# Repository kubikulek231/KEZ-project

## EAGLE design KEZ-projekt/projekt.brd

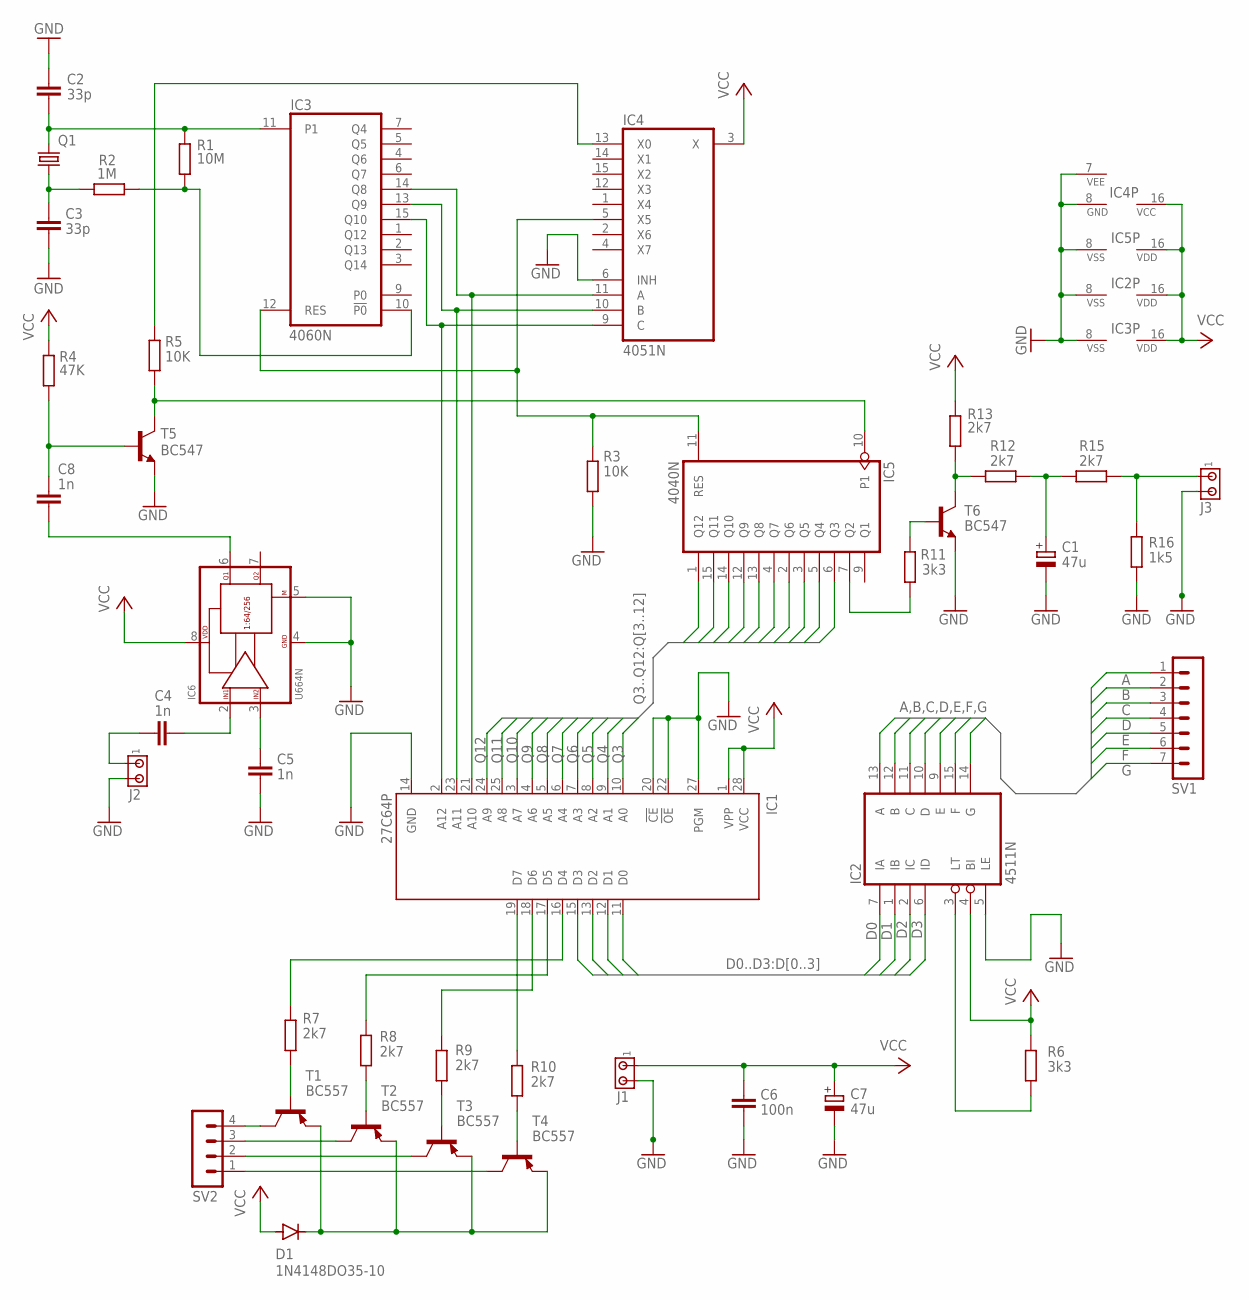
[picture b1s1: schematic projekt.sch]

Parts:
C1, C7: 47u; E2,5-6
C2, C3: 33p; C025-025X050
C4, C5, C8: 1n; C025-025X050
C6: 100n; C025-025X050
D1: 1N4148DO35-10; DO35-10
IC1: 27C64P; DIL28-6
IC2: 4511N; DIL16
IC3: 4060N; DIL16
IC4: 4051N; DIL16
IC5: 4040N; DIL16
IC6: U664N; DIL08
J1, J2, J3: MTA02-100; 10X02MTA
Q1: CRYSTALHC49S; HC49/S
R1: 10M; 0207/10
R2: 1M; 0207/10
R3, R5: 10K; 0207/10
R4: 47K; 0207/10
R6, R11: 3k3; 0207/10
R7, R8, R9, R10, R12, R13, R15: 2k7; 0207/10
R16: 1k5; 0207/10
SV1: MA07-1
SV2: MA04-1
T1, T2, T3, T4: BC557; TO92
T5, T6: BC547; TO92

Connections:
A: IC2.13 (A), SV1.1
B: IC2.12 (B), SV1.2
C: IC2.11 (C), SV1.3
D: IC2.10 (D), SV1.4
D0: IC1.11 (D0), IC2.7 (IA)
D1: IC1.12 (D1), IC2.1 (IB)
D2: IC1.13 (D2), IC2.2 (IC)
D3: IC1.15 (D3), IC2.6 (ID)
E: IC2.9 (E), SV1.5
F: IC2.15 (F), SV1.6
G: IC2.14 (G), SV1.7
GND: C1.-, C2.1, C3.2, C5.2, C6.2, C7.-, IC1.14 (GND), IC1.20 (!CE), IC1.22 (!OE), IC1.27 (PGM), IC2.5 (LE), IC2.8 (VSS), IC3.8 (VSS), IC4.6 (INH), IC4.7 (VEE), IC4.8 (GND), IC5.8 (VSS), IC6.4 (GND), IC6.5 (FAKT), J1.2, J2.2, J3.2, R3.1, R16.1, T5.1 (E), T6.1 (E)
unnamed: C2.2, IC3.11 (P1), Q1.2, R1.2
unnamed: C3.1, Q1.1, R2.2
unnamed: IC3.10 (!P0), R1.1, R2.1
unnamed: IC1.21 (A10), IC3.14 (Q8), IC4.11 (A)
unnamed: IC1.23 (A11), IC3.13 (Q9), IC4.10 (B)
unnamed: IC1.2 (A12), IC3.15 (Q10), IC4.9 (C)
unnamed: IC3.12 (RES), IC4.5 (X5), IC5.11 (RES), R3.2
unnamed: C8.1, R4.1, T5.2 (B)
unnamed: C8.2, IC6.6 (O1)
unnamed: C5.1, IC6.3 (I2)
unnamed: C4.2, IC6.2 (I1)
unnamed: IC5.10 (P1), R5.1, T5.3 (C)
unnamed: C4.1, J2.1
unnamed: R12.1, R13.2, T6.3 (C)
unnamed: IC2.3 (LT), R6.2
unnamed: IC1.17 (D5), R8.2
unnamed: IC1.16 (D4), R7.2
unnamed: IC1.18 (D6), R9.2
unnamed: IC1.19 (D7), R10.2
unnamed: D1.C, T1.1 (E), T2.1 (E), T3.1 (E), T4.1 (E)
unnamed: R9.1, T3.2 (B)
unnamed: R8.1, T2.2 (B)
unnamed: R7.1, T1.2 (B)
unnamed: SV2.4, T1.3 (C)
unnamed: SV2.3, T2.3 (C)
unnamed: SV2.2, T3.3 (C)
unnamed: SV2.1, T4.3 (C)
unnamed: R10.1, T4.2 (B)
unnamed: IC5.7 (Q2), R11.1
unnamed: R11.2, T6.2 (B)
unnamed: C1.+, R12.2, R15.1
unnamed: J3.1, R15.2, R16.2
unnamed: IC4.13 (X0), R5.2
Q3: IC1.10 (A0), IC5.6 (Q3)
Q4: IC1.9 (A1), IC5.5 (Q4)
Q5: IC1.8 (A2), IC5.3 (Q5)
Q6: IC1.7 (A3), IC5.2 (Q6)
Q7: IC1.6 (A4), IC5.4 (Q7)
Q8: IC1.5 (A5), IC5.13 (Q8)
Q9: IC1.4 (A6), IC5.12 (Q9)
Q10: IC1.3 (A7), IC5.14 (Q10)
Q11: IC1.25 (A8), IC5.15 (Q11)
Q12: IC1.24 (A9), IC5.1 (Q12)
VCC: C6.1, C7.+, D1.A, IC1.1 (VPP), IC1.28 (VCC), IC2.4 (BI), IC2.16 (VDD), IC3.16 (VDD), IC4.3 (X), IC4.16 (VCC), IC5.16 (VDD), IC6.8 (VPP), J1.1, R4.2, R6.1, R13.1

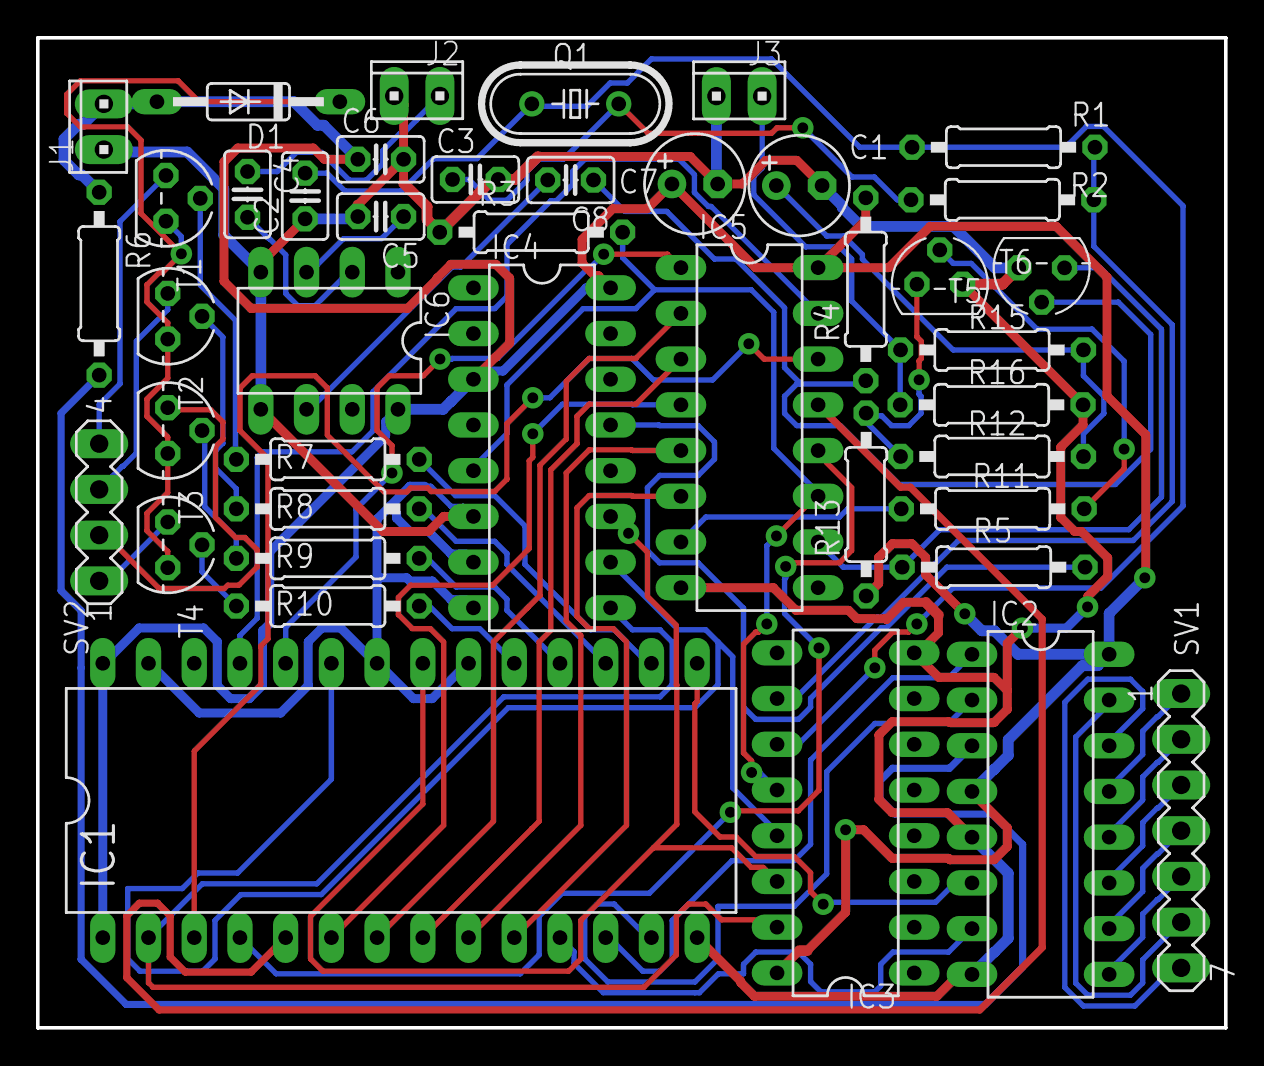
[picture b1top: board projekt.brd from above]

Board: 2 copper layers, 66.0 x 55.0 mm, 42 parts (0 on the bottom side), 56 nets.

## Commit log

2023-04-13 not constant
2023-04-14 completed - class 4
